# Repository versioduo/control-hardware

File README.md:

# control-hardware

⚙️ Instrument Controller

## Board

## Schematic

[PDF](control.pdf)

## Bill Of Materials

[Interactive BOM](https://htmlpreview.github.io/?https://github.com/versioduo/control-hardware/main/control-bom.html)

# Copying
Anyone can use this public domain work without having to seek authorisation, no one can ever own it.

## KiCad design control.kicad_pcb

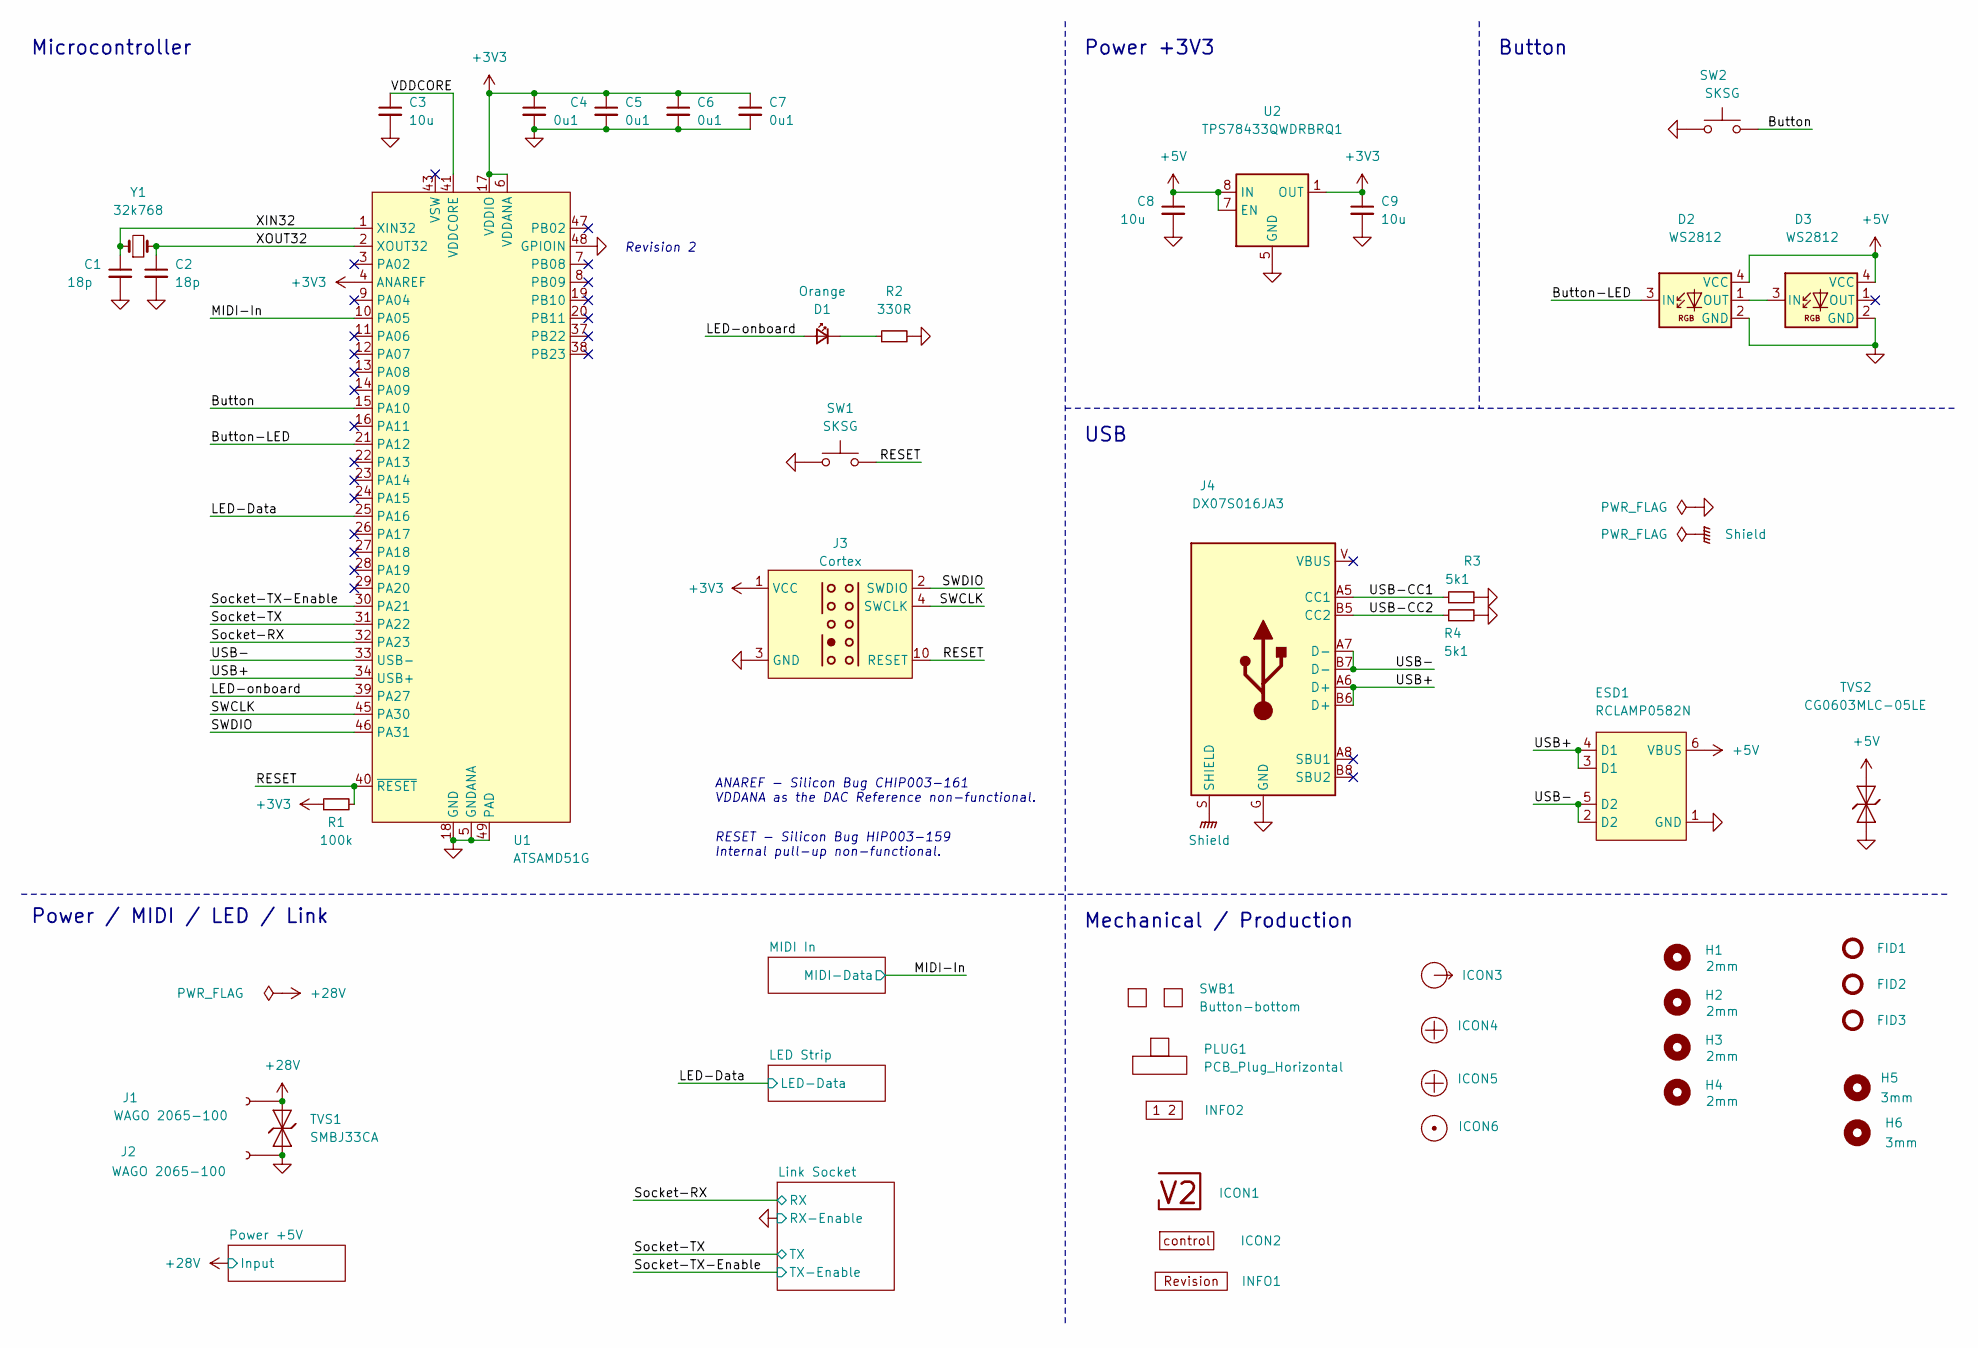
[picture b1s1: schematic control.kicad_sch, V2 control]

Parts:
C1, C2: 18p; C_1608; Rating 50V; Mouser 810-CGA3E2C0G1H180J
C3: 10u; C_1608; Rating 10V; Mouser 810-C1608X6S1A106M
C4, C5, C6, C7: 0u1; C_1608; Rating 50V; Mouser 810-CGA3E2X7R1H104MA
C8, C9: 10u; C_2012; Rating 25V; Mouser 810-C2012X5R1E106K
D1: Orange; LED_1608; Rating 605nm; Mouser 755-SML-D12D1WT86
D2, D3: WS2812; WS2812-2020; Rating 15mA; LCSC C965555
ESD1: RCLAMP0582N; SLP1210N6; Rating 20kV; Mouser 947-RCLAMP0582N.TCT
FID1, FID2, FID3: Fiducial_Paste; Fiducial_0.5mm_Mask1mm_Paste
H1, H2, H3, H4: 2mm; MountingHole_2mm
H5, H6: 3mm; MountingHole_3mm
ICON1: V2-logo; Logo_Small
ICON2: Board_control; Board_control_Small
ICON3: Arrow_Out
ICON4, ICON5: Plus; Plus_Small
ICON6: Dot; Dot_Small
INFO1: Revision
INFO2: Layer_Numbers-4
J1, J2: WAGO 2065-100; 2065-100; Rating 9A
J3: Cortex
J4: DX07S016JA3; JAE_DX07S016JA3; Rating USB2.0; Mouser 656-DX07S016JA3R1500
PLUG1: PCB_Plug_Horizontal
R1: 100k; R_1608; Rating 100mW; Mouser 71-CRCW0603100KFKEAC
R2: 330R; R_1608; Rating 100mW; Mouser 71-CRCW0603330RFKEAC
R3, R4: 5k1; R_1608; Rating 100mW; Mouser 71-CRCW06035K10FKEAC
SW1, SW2: SKSG; Rating 1.6N; Mouser 688-SKSGACE010
SWB1: Button-bottom; PCB_Button-bottom
TVS1: SMBJ33CA; D_SMB; Rating 33V; Mouser 652-SMBJ33CA-Q
TVS2: CG0603MLC-05LE; D_1608; Rating 5V; Mouser 652-CG0603MLC-05LE
U1: ATSAMD51G; QFN-48-1EP_7x7mm_P0.5mm_EP5.45x5.45mm_ThermalVias; Rating Cortex-M4F; Mouser 556-ATSAMD51G19AMU
U2: TPS78433QWDRBRQ1; VSON-8-1_3x3mm_P0.65_EP1.65x2.4mm; Rating 300mA; Mouser 595-TPS78433QWDRBRQ1
Y1: 32k768; Crystal_SMD_3215-2Pin_3.2x1.5mm; Rating 10ppm; Mouser 815-ABS0716632.768KT

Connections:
+3V3: C4.1, C5.1, C6.1, C7.1, C9.1, J3.1 (VCC), R1.1, U1.4 (ANAREF), U1.6 (VDDANA), U1.17 (VDDIO), U1.36 (VDDIO), U1.44 (VDDIO), U2.1 (OUT); also elsewhere on the board
+5V: C8.1, D2.4 (VCC), D3.4 (VCC), ESD1.6 (VBUS), TVS2.2 (A), U2.6 (EN), U2.7 (EN), U2.8 (IN); also elsewhere on the board
+28V: J1.1, TVS1.2 (A); also elsewhere on the board
/Button: SW2.2, U1.15 (PA10)
/Button-LED: D2.3 (IN), U1.21 (PA12)
/LED-Data: U1.25 (PA16); also elsewhere on the board
/LED-onboard: D1.2 (A), U1.39 (PA27)
/MIDI-In: U1.10 (PA05); also elsewhere on the board
/RESET: J3.10 (RESET), R1.2, SW1.2, U1.40 (~RESET)
/SWCLK: J3.4 (SWCLK), U1.45 (PA30)
/SWDIO: J3.2 (SWDIO), U1.46 (PA31)
/Shield: J4.S (SHIELD)
/Socket-RX: U1.32 (PA23); also elsewhere on the board
/Socket-TX: U1.31 (PA22); also elsewhere on the board
/Socket-TX-Enable: U1.30 (PA21); also elsewhere on the board
/USB+: ESD1.3 (D1), ESD1.4 (D1), J4.A6 (D+), J4.B6 (D+), U1.34 (USB+)
/USB-: ESD1.2 (D2), ESD1.5 (D2), J4.A7 (D-), J4.B7 (D-), U1.33 (USB-)
/USB-CC1: J4.A5 (CC1), R3.1
/USB-CC2: J4.B5 (CC2), R4.1
/VDDCORE: C3.1, U1.41 (VDDCORE)
/XIN32: C1.1, U1.1 (XIN32), Y1.1
/XOUT32: C2.1, U1.2 (XOUT32), Y1.2
GND: C1.2, C2.2, C3.2, C4.2, C5.2, C6.2, C7.2, C8.2, C9.2, D2.2 (GND), D3.2 (GND), ESD1.1 (GND), J2.1, J3.3 (GND), J3.5 (GND), J4.G (GND), R2.2, R3.2, R4.2, SW1.1, SW2.1, TVS1.1 (K), TVS2.1 (K), U1.5 (GNDANA), U1.18 (GND), U1.35 (GND), U1.42 (GND), U1.48 (GPIOIN), U1.49 (PAD), U2.5 (GND), U2.9 (GND); also elsewhere on the board
unnamed: D1.1 (K), R2.1
unnamed: D2.1 (OUT), D3.3 (IN)

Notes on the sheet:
ANAREF - ﻿Silicon Bug CHIP003-161 VDDANA as the DAC Reference non-functional.
Power / MIDI / LED / Link
RESET - ﻿Silicon Bug HIP003-159 Internal pull-up non-functional.
Button
Revision 2
Power +3V3
Mechanical / Production
Microcontroller
USB

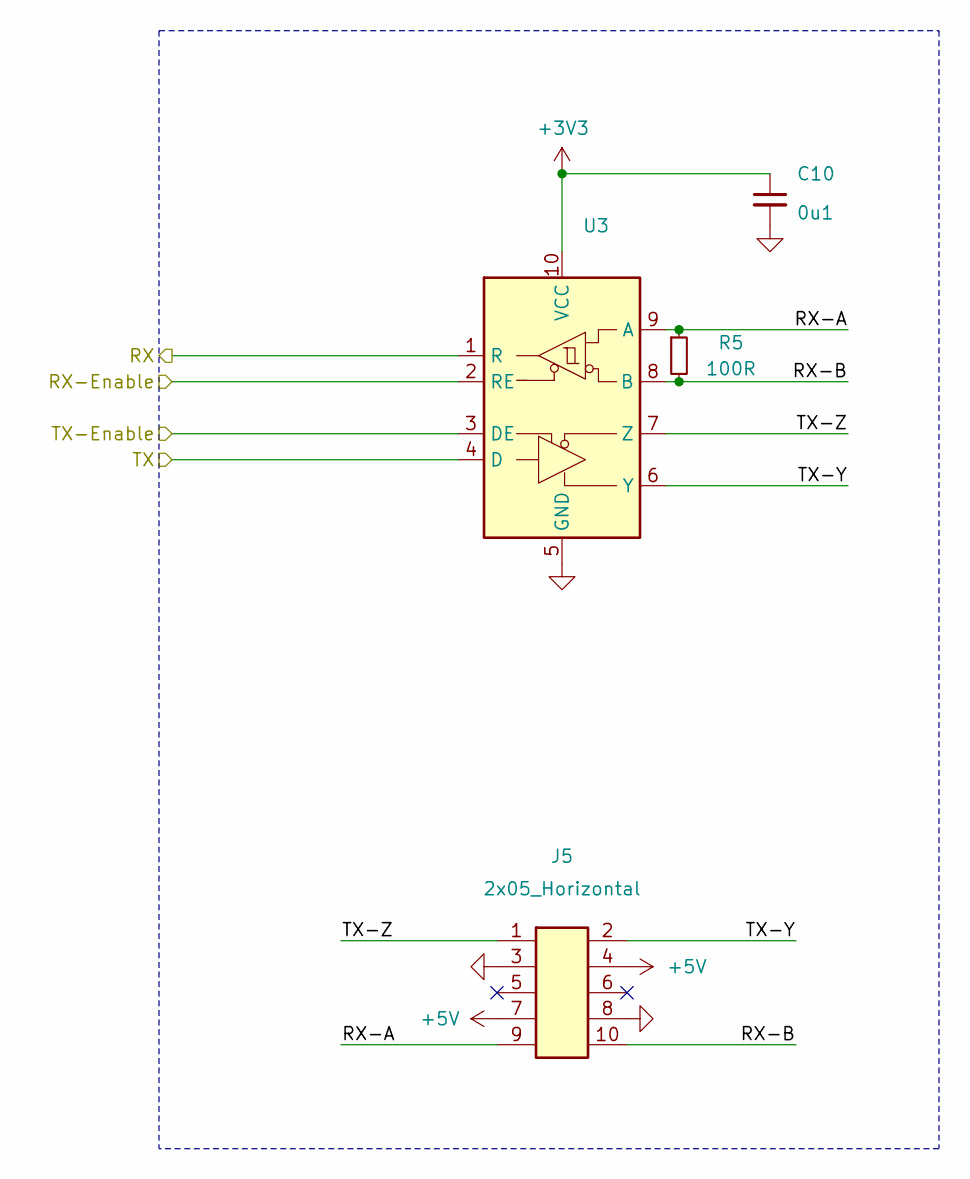
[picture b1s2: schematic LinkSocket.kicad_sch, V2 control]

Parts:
C10: 0u1; C_1608; Rating 50V; Mouser 810-CGA3E2X7R1H104MA
J5: 2x05_Horizontal; PinHeader_2x05_P1.27mm_Horizontal; Rating 1A; Mouser 649-200211120001T4LF
R5: 100R; R_1608; Rating 330mW; Mouser 71-CRCW0603100RFKEAH
U3: VSON-10-4-1EP_3x3mm_P0.5mm_EP1.65x2.4mm_ThermalVias

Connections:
+3V3: C10.1, U3.10 (VCC); also elsewhere on the board
+5V: J5.4, J5.7; also elsewhere on the board
/Link Socket/RX-A: J5.9, R5.1, U3.9 (A)
/Link Socket/RX-B: J5.10, R5.2, U3.8 (B)
/Link Socket/TX-Y: J5.2, U3.6 (Y)
/Link Socket/TX-Z: J5.1, U3.7 (Z)
/Socket-RX: U3.1 (R); also elsewhere on the board
/Socket-TX: U3.4 (D); also elsewhere on the board
/Socket-TX-Enable: U3.3 (DE); also elsewhere on the board
GND: C10.2, J5.3, J5.8, U3.2 (RE), U3.5 (GND), U3.11 (GND); also elsewhere on the board

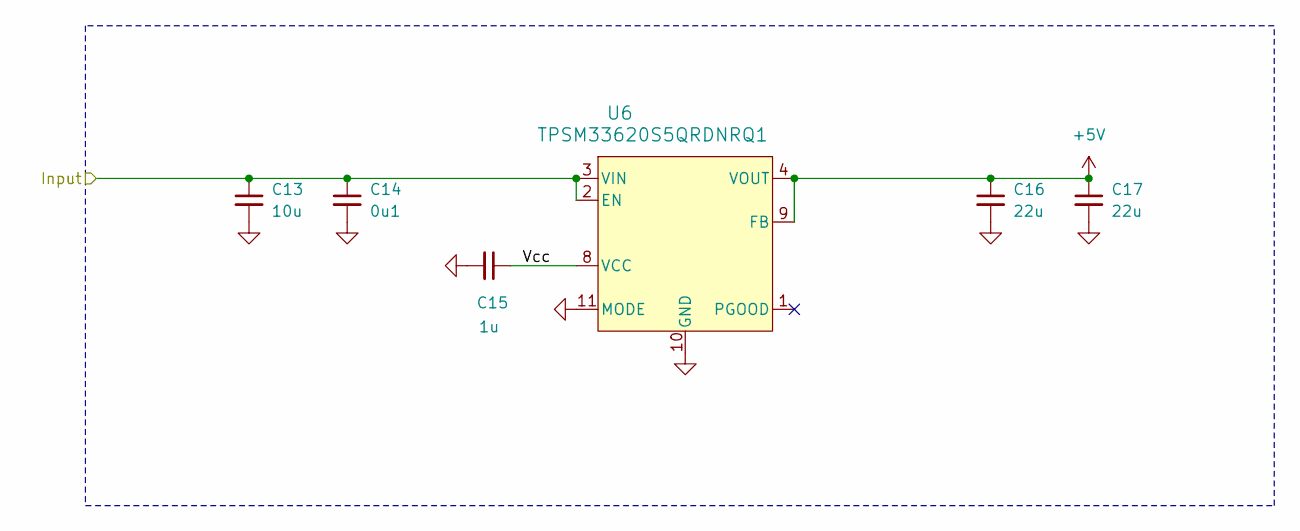
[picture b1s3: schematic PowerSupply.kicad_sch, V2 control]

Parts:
C13: 10u; C_3225; Rating 50V; Mouser 810-CNC6P1X7R1H106K2
C14: 0u1; C_1608; Rating 50V; Mouser 810-CGA3E2X7R1H104MA
C15: 1u; C_1608; Rating 50V; Mouser 810-CGA3E3X7R1H105K0
C16, C17: 22u; C_3225; Rating 25V; Mouser 810-CGA6P3X7R1E226M5
U6: TPSM33620S5QRDNRQ1; QFN-11; Rating 2A; Mouser 595-SM33620S5QRDNRQ1

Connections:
+5V: C16.1, C17.1, U6.4 (VOUT), U6.9 (FB); also elsewhere on the board
+28V: C13.1, C14.1, U6.2 (EN), U6.3 (VIN); also elsewhere on the board
/Power +5V/Vcc: C15.1, U6.8 (VCC)
GND: C13.2, C14.2, C15.2, C16.2, C17.2, U6.10 (GND), U6.11 (MODE); also elsewhere on the board

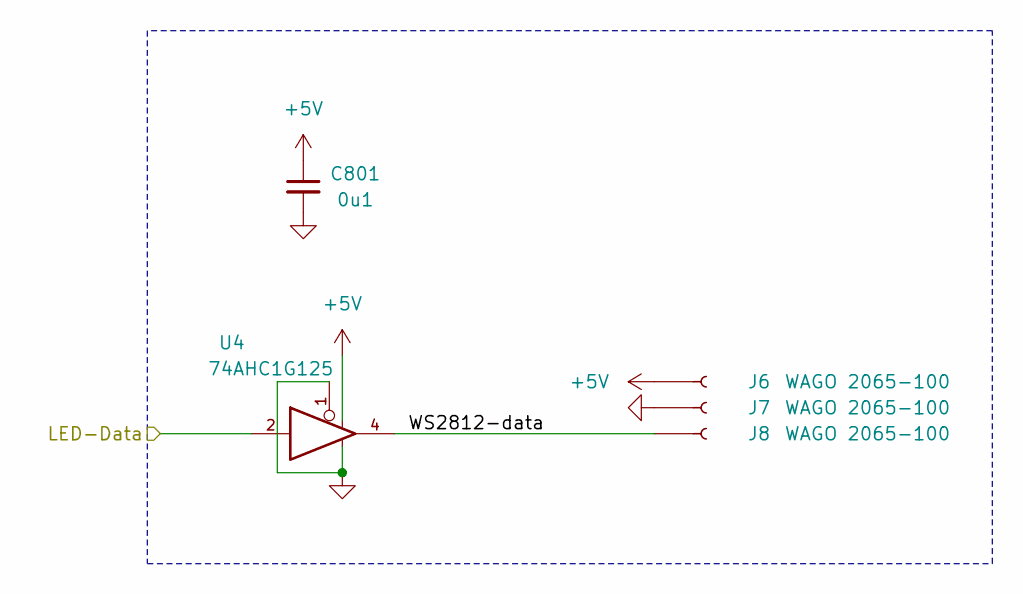
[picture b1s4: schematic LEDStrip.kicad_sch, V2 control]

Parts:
C801: 0u1; C_1608; Rating 50V; Mouser 810-CGA3E2X7R1H104MA
J6, J7, J8: WAGO 2065-100; 2065-100; Rating 9A
U4: 74AHC1G125; SOT-23-5; Rating 8mA; Mouser 595-SN74AHC1G125DBVR

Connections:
+5V: C801.1, J6.1, U4.5; also elsewhere on the board
/LED Strip/WS2812-data: J8.1, U4.4
/LED-Data: U4.2; also elsewhere on the board
GND: C801.2, J7.1, U4.1, U4.3; also elsewhere on the board

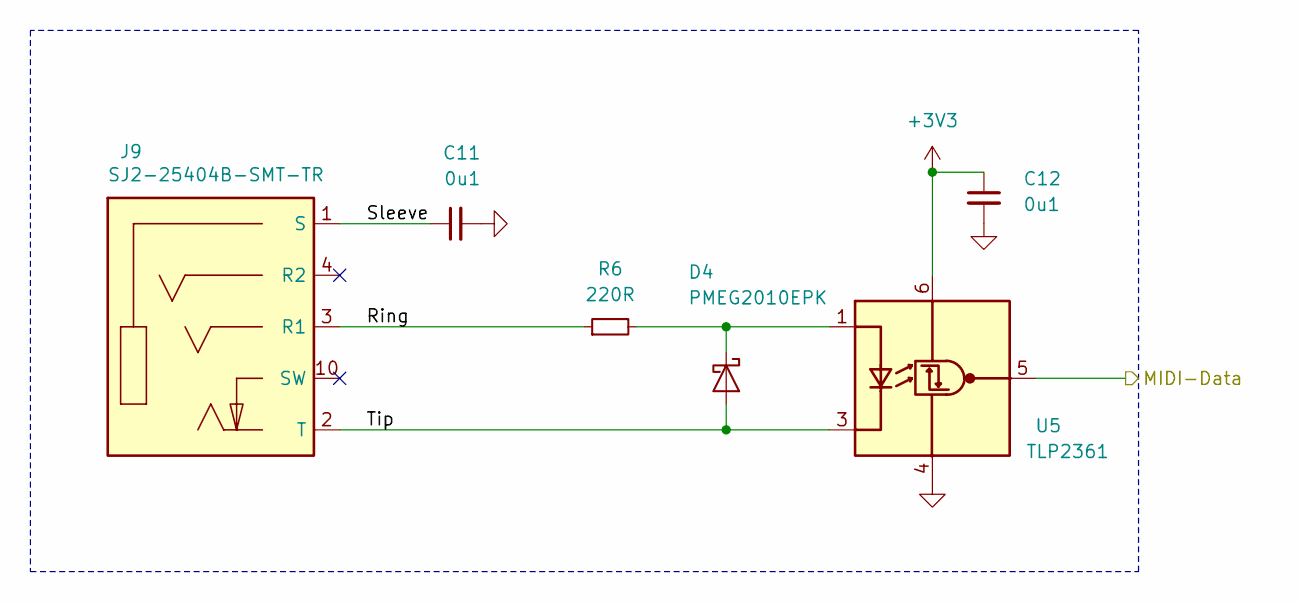
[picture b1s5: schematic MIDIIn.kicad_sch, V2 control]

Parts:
C11, C12: 0u1; C_1608; Rating 50V; Mouser 810-CGA3E2X7R1H104MA
D4: PMEG2010EPK; D_SOD-1608; Rating 20V; Mouser 771-PMEG2010EPK
J9: SJ2-25404B-SMT-TR; CUI_SJ2-25404B-SMT-TR; Rating 2.5mm; Mouser 490-SJ2-25404BSMT-TR
R6: 220R; R_1608; Rating 330mW; Mouser 71-CRCW0603220RFKEAH
U5: TLP2361; SO-5-6_4.55x3.7mm_P1.27mm; Rating 15Mbps; Mouser 757-TLP2361TPRE

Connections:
+3V3: C12.1, U5.6 (VDD); also elsewhere on the board
/MIDI In/Ring: J9.3 (R1), R6.1
/MIDI In/Sleeve: C11.1, J9.1 (S)
/MIDI In/Tip: D4.2 (A), J9.2 (T), U5.3 (K)
/MIDI-In: U5.5 (VO); also elsewhere on the board
GND: C11.2, C12.2, U5.4 (GND); also elsewhere on the board
unnamed: D4.1 (K), R6.2, U5.1 (A)

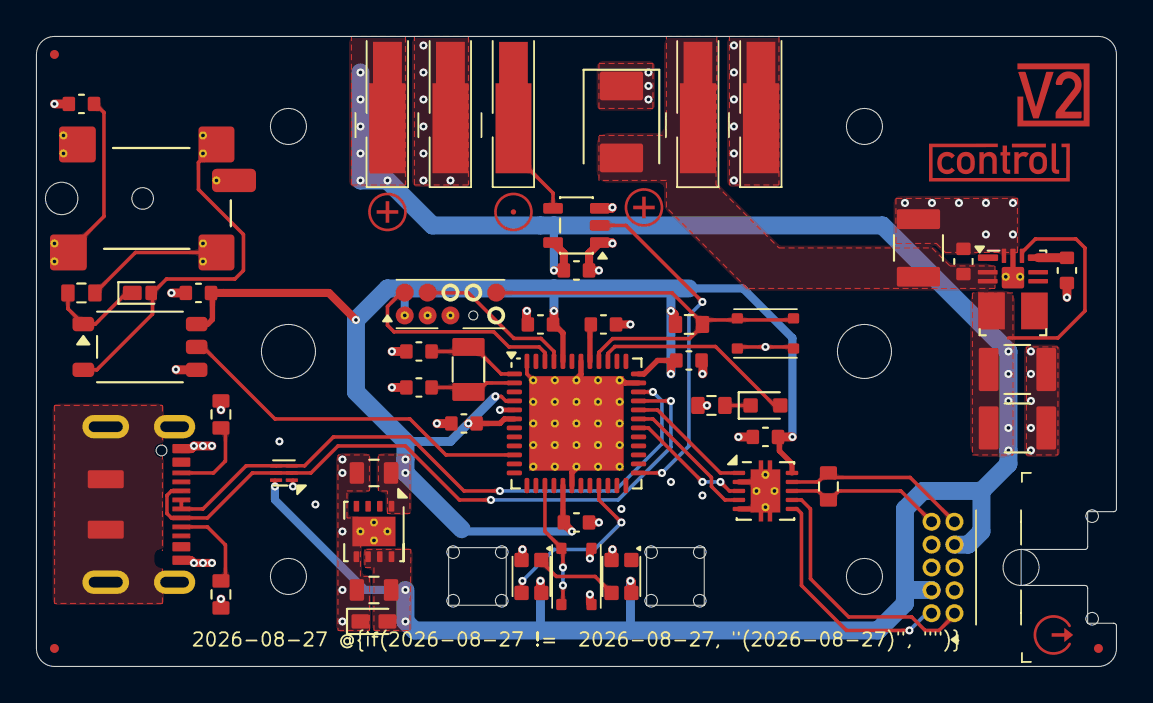
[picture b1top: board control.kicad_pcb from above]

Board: 4 copper layers, 60.0 x 35.0 mm, 68 parts (0 on the bottom side), 34 nets.

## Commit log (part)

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2023-08-08 Import
2024-03-28 Update to Kicad 8
2024-03-28 Update DCDC
2024-06-20 Replace icons
2024-07-17 Update TRS socket
2025-10-27 Refresh
